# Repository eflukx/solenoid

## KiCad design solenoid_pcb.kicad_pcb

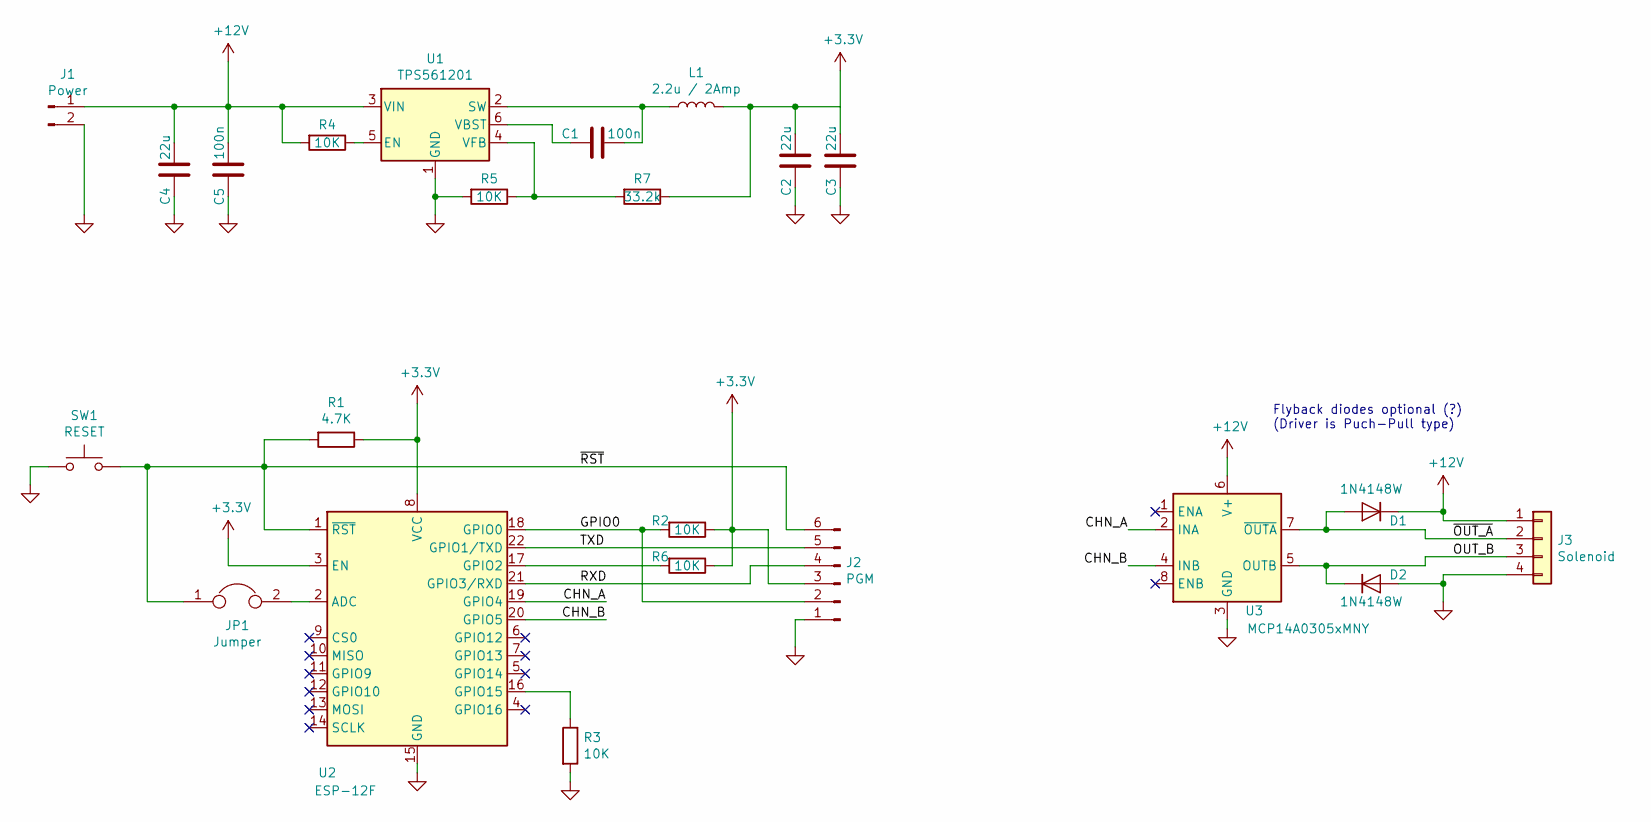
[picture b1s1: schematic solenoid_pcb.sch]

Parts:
C1, C5: 100n; C_0603_1608Metric
C2, C3, C4: 22u; C_0805_2012Metric
D1, D2: 1N4148W; D_SOD-123
J1: Power; PinHeader_1x02_P2.54mm_Vertical
J2: PGM; PinHeader_1x06_P2.54mm_Vertical
J3: Solenoid; PinHeader_1x04_P2.54mm_Vertical
JP1: Jumper; SolderJumper-2_P1.3mm_Open_RoundedPad1.0x1.5mm
L1: 2.2u / 2Amp; L_Bourns-SRN4018
R1: 4.7K; R_0603_1608Metric
R2, R3, R4, R5, R6: 10K; R_0603_1608Metric
R7: 33.2k; R_0603_1608Metric
SW1: RESET; SW_SPST_B3U-1000P-B
U1: TPS561201; SOT-23-6
U2: ESP-12F; ESP-12E
U3: MCP14A0305xMNY; WDFN-8-1EP_3x2mm_P0.5mm_EP1.3x1.4mm

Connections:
+3V3: C2.1, C3.1, J2.3, L1.2, R1.1, R2.1, R6.1, R7.1, U2.3 (EN), U2.8 (VCC)
+12V: C4.1, C5.1, D1.1 (K), J1.1, J3.1, R4.2, U1.3 (VIN), U3.6 (V+)
/CHN_A: U2.19 (GPIO4), U3.2 (INA)
/CHN_B: U2.20 (GPIO5), U3.4 (INB)
/GPIO0: J2.2, R2.2, U2.18 (GPIO0)
/OUT_B: D2.1 (K), J3.3, U3.5 (OUTB)
/RXD: J2.4, U2.21 (GPIO3/RXD)
/TXD: J2.5, U2.22 (GPIO1/TXD)
/~OUT_A: D1.2 (A), J3.2, U3.7 (~OUTA)
/~RST: J2.6, JP1.1, R1.2, SW1.2, U2.1 (~RST)
GND: C2.2, C3.2, C4.2, C5.2, D2.2 (A), J1.2, J2.1, J3.4, R3.2, R5.2, SW1.1, U1.1 (GND), U2.15 (GND), U3.3 (GND), U3.9 (GND)
unnamed: C1.1, L1.1, U1.2 (SW)
unnamed: C1.2, U1.6 (VBST)
unnamed: JP1.2, U2.2 (ADC)
unnamed: R3.1, U2.16 (GPIO15)
unnamed: R4.1, U1.5 (EN)
unnamed: R5.1, R7.2, U1.4 (VFB)
unnamed: R6.2, U2.17 (GPIO2)

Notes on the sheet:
Flyback diodes optional (?) (Driver is Puch-Pull type)

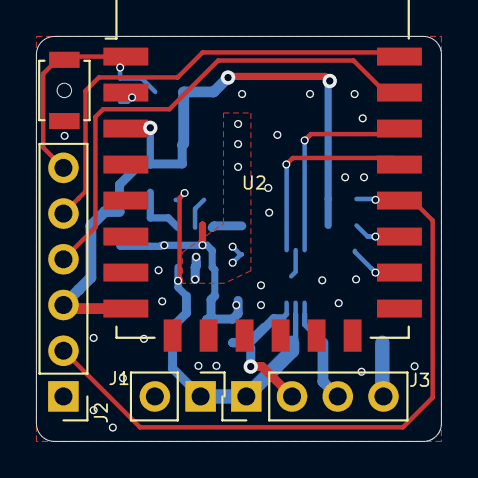
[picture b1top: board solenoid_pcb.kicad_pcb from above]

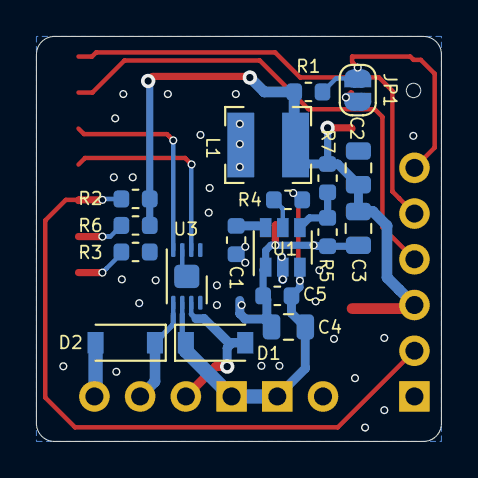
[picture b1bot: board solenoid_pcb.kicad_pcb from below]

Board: 2 copper layers, 22.5 x 22.5 mm, 23 parts (18 on the bottom side), 18 nets.

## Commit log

2019-12-21 corrected VCC
2019-12-21 no -bak files
2019-12-21 tweaked the vc & ground planes
2019-12-21 more tweaks
2019-12-22 Dingen en zaken
    3.3v heeft een eigen power symbol (ipv global label)
    `sig` label locla gemaakt, kleinigheidje
    2mm header is niet standaard! (2,54mm / 100mil wel)
    Ook ff normale run-off-the-mill 6mm switch erin gestopt
    Alle headers staan nu op het zelfde 2.54mm grid
    Weet je zeker dat de footprint van je inductor klopt?
2019-12-23 Add esp32-pico-d4 lib (as submodule)
2019-12-23 Create smaller board, components to back (except ESP12), 2 channel output
2019-12-23 Apply real small routing update (gnd via's)
2019-12-23 Add ESP12 3D model
